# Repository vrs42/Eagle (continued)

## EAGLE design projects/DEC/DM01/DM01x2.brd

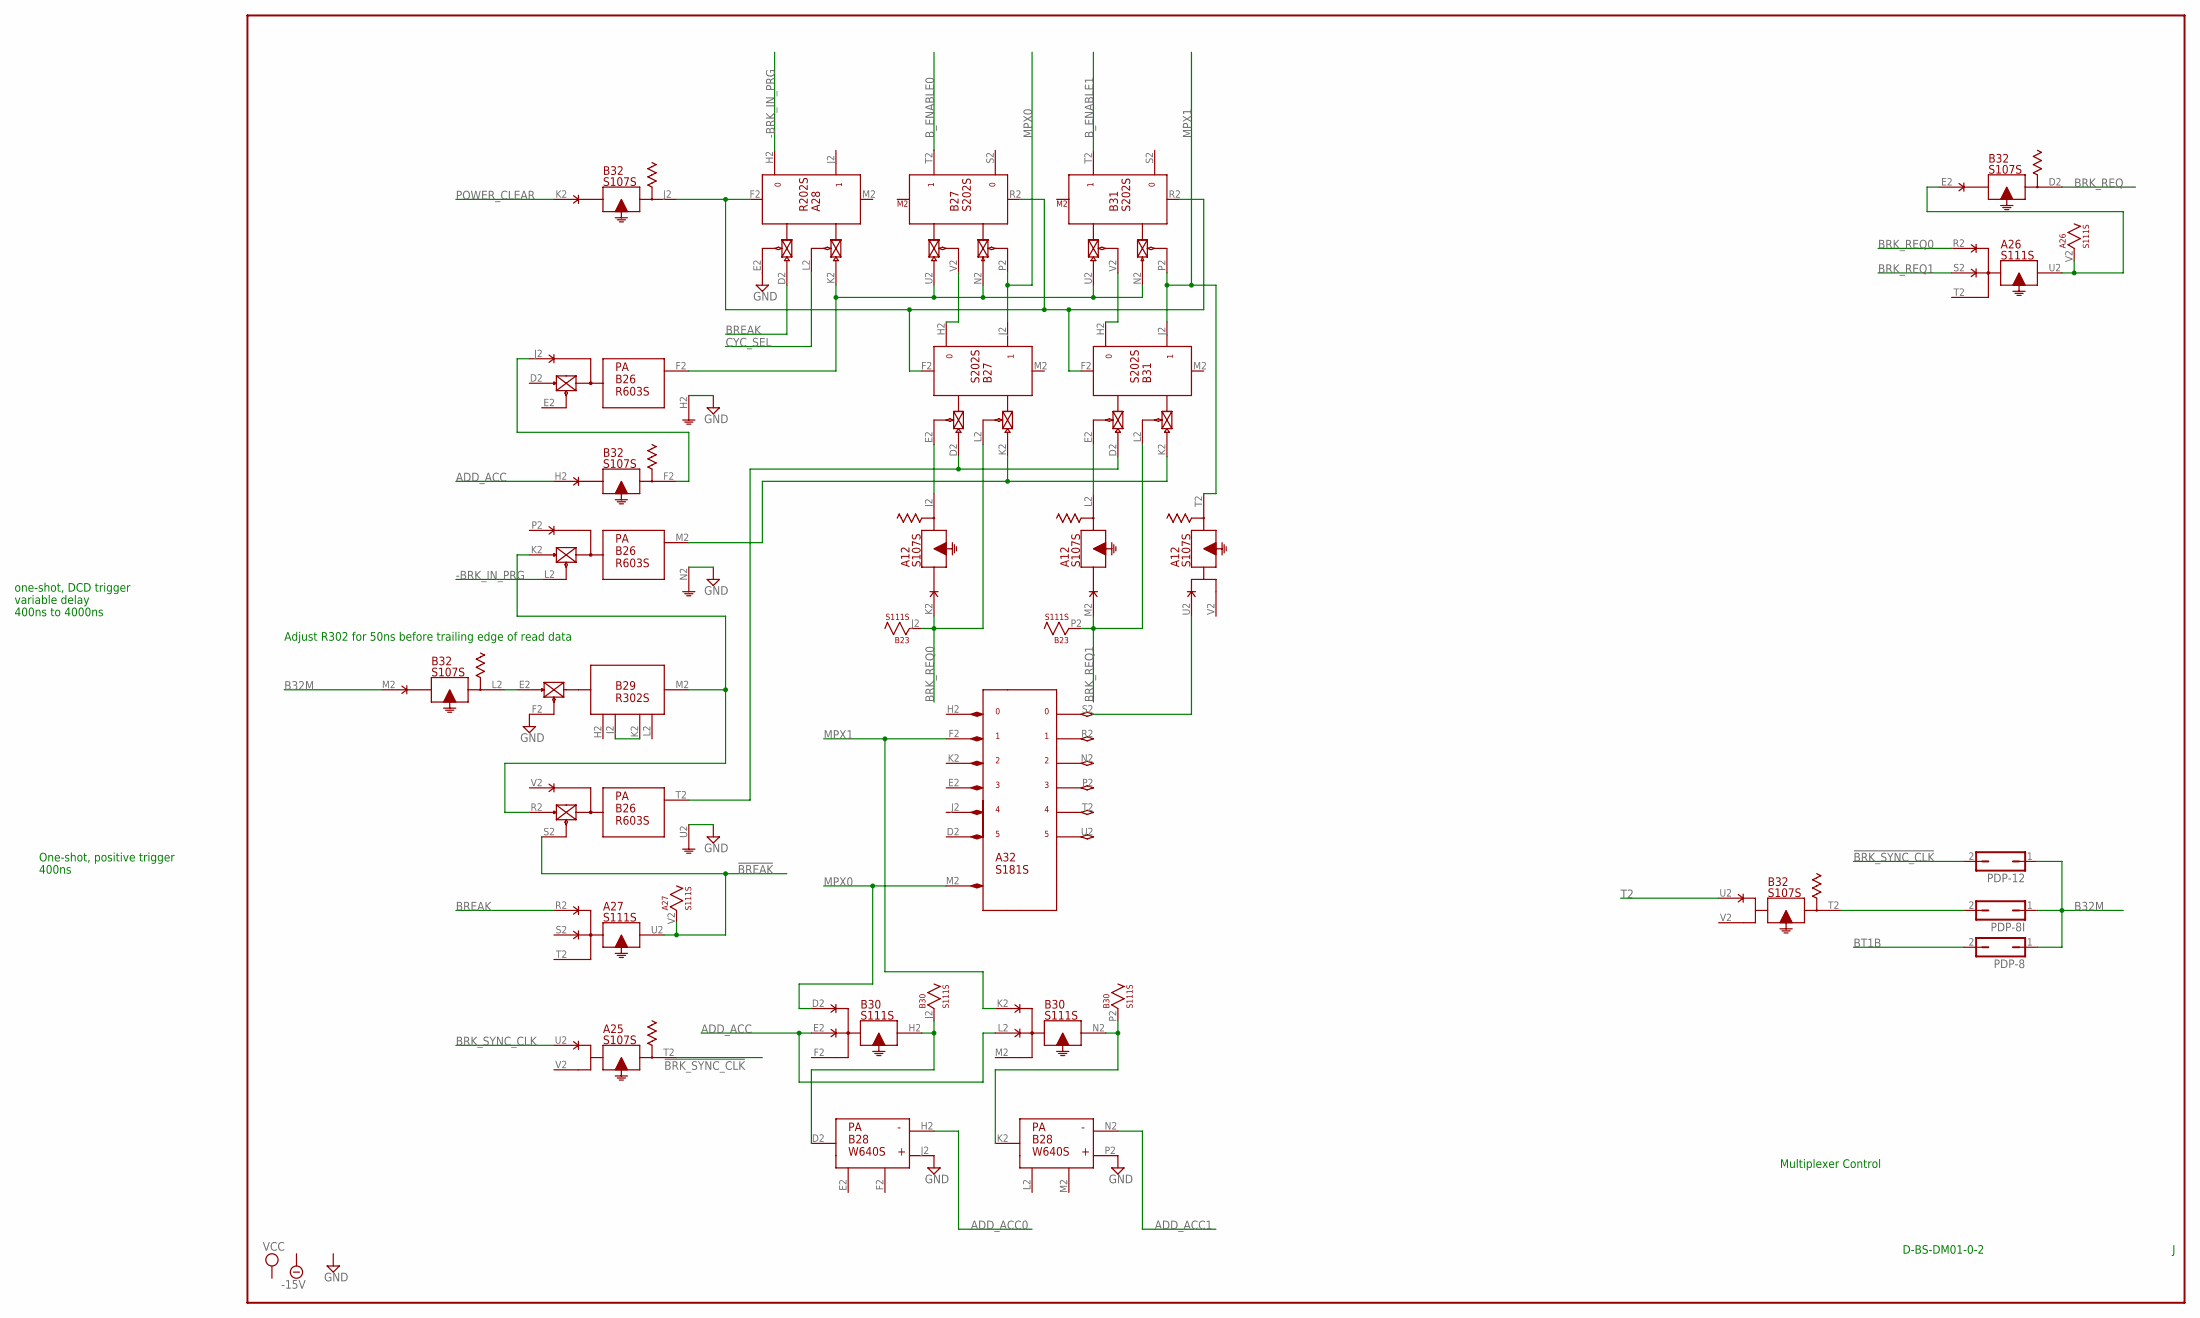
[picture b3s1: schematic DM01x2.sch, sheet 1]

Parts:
A12, A25: S107S; H807S
A26, A27: S111S; H807S
A28: R202S; H807S
A32: S181S; H807S
B23, B30: S111S; H807S
B26: R603S; H807S
B27, B31: S202S; H807S
B28: W640S; H807S
B29: R302S; H807S
B32: S107S; H807S
PDP-8, PDP-8I, PDP-12: JP1Q; JP1

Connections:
!BREAK: A27.U2, A27.V2, B26.S2 (EN0)
!BRK_SYNC_CLK: A25.T2, PDP-12.2
-15V: A12.B2 (-15V), A25.B2 (-15V), A26.B2 (-15V), A27.B2 (-15V), A28.B2 (-15V), A32.B2 (-15V), B23.B2 (-15V), B26.B2 (-15V), B27.B2 (-15V), B28.B2 (-15V), B29.B2 (-15V), B30.B2 (-15V), B31.B2 (-15V), B32.B2 (-15V); also elsewhere on the board
-BRK_IN_PRG: A28.H2 (0), B26.L2 (EN0)
ADD_ACC: B30.E2, B30.L2, B32.H2; also elsewhere on the board
ADD_ACC0: B28.H2 (H); also elsewhere on the board
ADD_ACC1: B28.N2 (H); also elsewhere on the board
B32M: B32.M2, PDP-8.1, PDP-8I.1, PDP-12.1
BREAK: A27.R2, A28.D2 (PU0); also elsewhere on the board
BRK_REQ: B32.D2; also elsewhere on the board
BRK_REQ0: A12.K2, A26.R2, B23.J2, B27.L2 (EN1); also elsewhere on the board
BRK_REQ1: A12.M2, A26.S2, B23.P2, B31.L2 (EN1); also elsewhere on the board
BRK_SYNC_CLK: A25.U2; also elsewhere on the board
BT1B: PDP-8.2; also elsewhere on the board
B_ENABLE0: B27.T2 (1); also elsewhere on the board
B_ENABLE1: B31.T2 (1); also elsewhere on the board
CYC_SEL: A28.L2 (EN1); also elsewhere on the board
GND: A12.C2 (GND), A25.C2 (GND), A26.C2 (GND), A27.C2 (GND), A28.C2 (GND), A28.E2 (EN0), A32.C2 (GND), B23.C2 (GND), B26.C2 (GND), B26.H2 (G), B26.N2 (G), B26.U2 (G), B27.C2 (GND), B28.C2 (GND), B28.J2 (J), B28.P2 (J), B29.C2 (GND), B29.F2 (F), B30.C2 (GND), B31.C2 (GND), B32.C2 (GND); also elsewhere on the board
MPX0: A32.M2 (M), B27.J2 (1), B27.P2 (EN0), B30.D2; also elsewhere on the board
MPX1: A12.T2, A32.F2 (F), B30.K2, B31.J2 (1), B31.P2 (EN0); also elsewhere on the board
unnamed: A28.F2 (RESET), B27.F2 (RESET), B27.R2 (RESET), B31.F2 (RESET), B31.R2 (RESET), B32.J2
unnamed: B26.J2, B32.F2
unnamed: B32.T2, PDP-8I.2
unnamed: B26.K2 (PU0), B26.R2 (PU0), B29.M2 (M)
unnamed: B27.H2 (0), B27.V2 (EN1)
unnamed: B31.H2 (0), B31.V2 (EN1)
unnamed: B26.M2 (O), B27.K2 (PU1), B31.K2 (PU1)
unnamed: A28.K2 (PU1), B26.F2 (O), B27.N2 (PU0), B27.U2 (PU1), B31.N2 (PU0), B31.U2 (PU1)
unnamed: A26.U2, A26.V2, B32.E2
unnamed: A12.J2, B27.E2 (EN0)
unnamed: A12.L2, B31.E2 (EN0)
unnamed: B28.D2 (D), B30.H2, B30.J2
unnamed: B26.T2 (O), B27.D2 (PU0), B31.D2 (PU0)
unnamed: B28.K2 (D), B30.N2, B30.P2
unnamed: A12.U2, A32.S2 (S)
unnamed: B29.E2 (E), B32.L2
unnamed: B29.J2 (J), B29.K2 (K)
POWER_CLEAR: B32.K2; also elsewhere on the board
T2: B32.U2; also elsewhere on the board
VCC: A12.A2 (VCC), A25.A2 (VCC), A26.A2 (VCC), A27.A2 (VCC), A28.A2 (VCC), A32.A2 (VCC), B23.A2 (VCC), B26.A2 (VCC), B27.A2 (VCC), B28.A2 (VCC), B29.A2 (VCC), B30.A2 (VCC), B31.A2 (VCC), B32.A2 (VCC); also elsewhere on the board

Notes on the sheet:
Multiplexer Control
D-BS-DM01-0-2
one-shot, DCD trigger
variable delay
400ns to 4000ns
400ns
One-shot, positive trigger
Adjust R302 for 50ns before trailing edge of read data

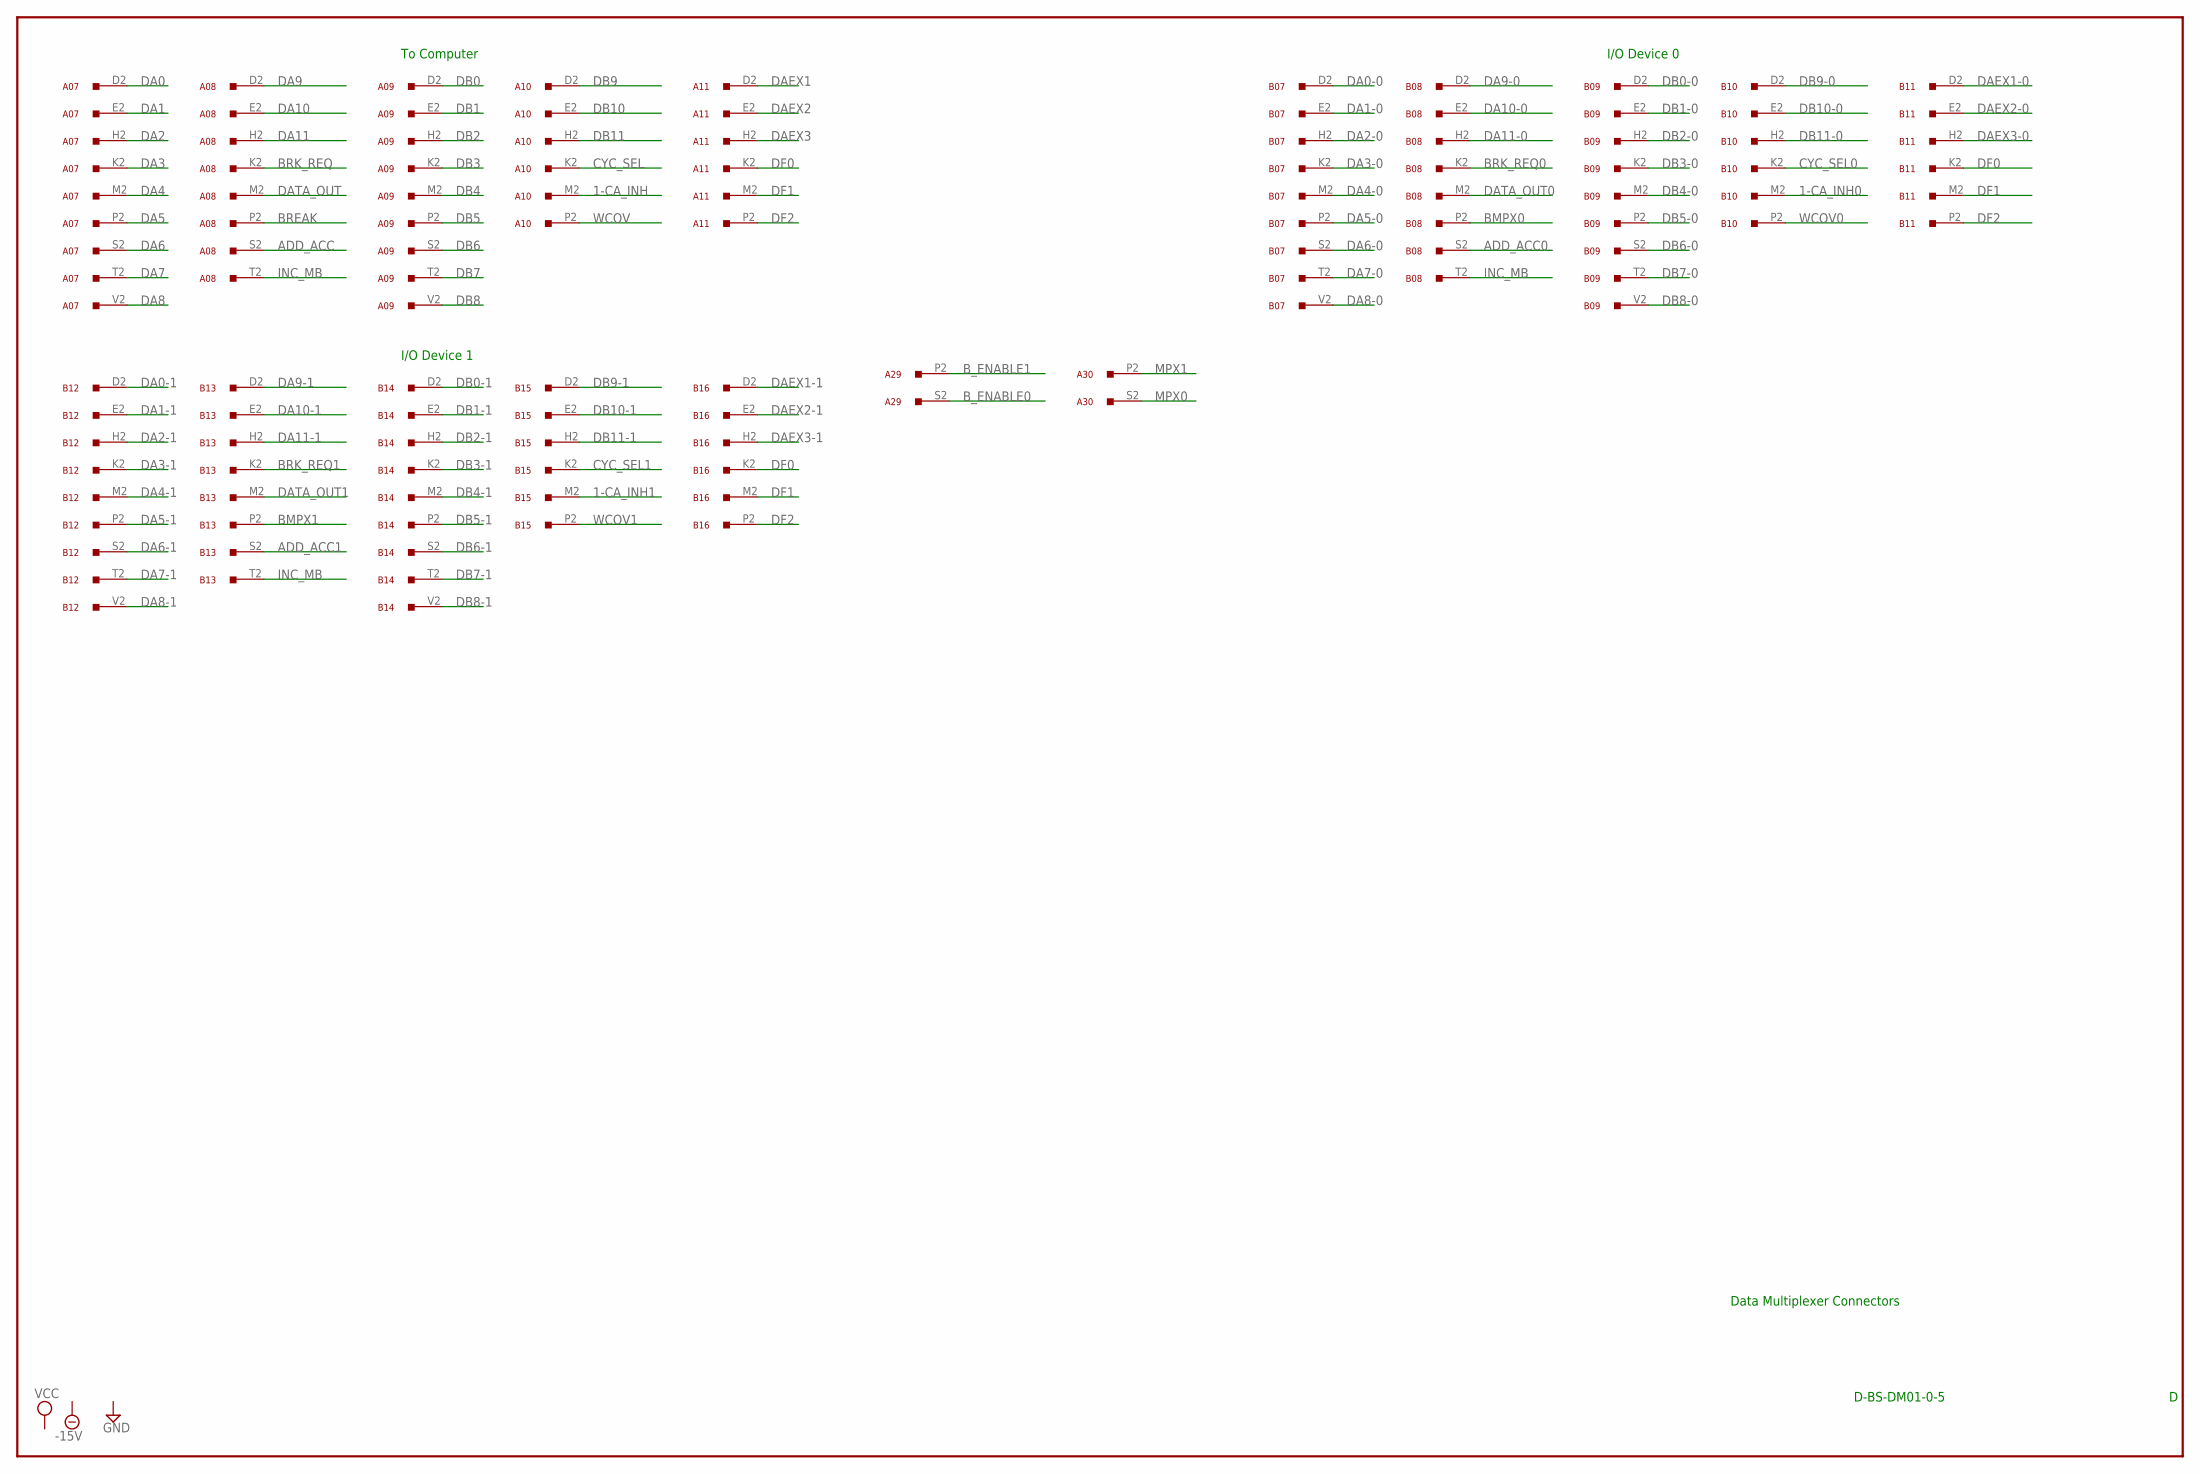
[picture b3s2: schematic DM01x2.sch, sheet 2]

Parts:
A07, A08, A09, A10, A11, A29, A30: W021S; H807S
B07, B08, B09, B10, B11, B12, B13, B14, B15, B16: W021S; H807S

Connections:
1-CA_INH: A10.M2; also elsewhere on the board
1-CA_INH0: B10.M2; also elsewhere on the board
1-CA_INH1: B15.M2; also elsewhere on the board
ADD_ACC: A08.S2; also elsewhere on the board
ADD_ACC0: B08.S2; also elsewhere on the board
ADD_ACC1: B13.S2; also elsewhere on the board
BMPX0: B08.P2; also elsewhere on the board
BMPX1: B13.P2; also elsewhere on the board
BREAK: A08.P2; also elsewhere on the board
BRK_REQ: A08.K2; also elsewhere on the board
BRK_REQ0: B08.K2; also elsewhere on the board
BRK_REQ1: B13.K2; also elsewhere on the board
B_ENABLE0: A29.S2; also elsewhere on the board
B_ENABLE1: A29.P2; also elsewhere on the board
CYC_SEL: A10.K2; also elsewhere on the board
CYC_SEL0: B10.K2; also elsewhere on the board
CYC_SEL1: B15.K2; also elsewhere on the board
DA0: A07.D2; also elsewhere on the board
DA0-0: B07.D2; also elsewhere on the board
DA0-1: B12.D2; also elsewhere on the board
DA1: A07.E2; also elsewhere on the board
DA1-0: B07.E2; also elsewhere on the board
DA1-1: B12.E2; also elsewhere on the board
DA2: A07.H2; also elsewhere on the board
DA2-0: B07.H2; also elsewhere on the board
DA2-1: B12.H2; also elsewhere on the board
DA3: A07.K2; also elsewhere on the board
DA3-0: B07.K2; also elsewhere on the board
DA3-1: B12.K2; also elsewhere on the board
DA4: A07.M2; also elsewhere on the board
DA4-0: B07.M2; also elsewhere on the board
DA4-1: B12.M2; also elsewhere on the board
DA5: A07.P2; also elsewhere on the board
DA5-0: B07.P2; also elsewhere on the board
DA5-1: B12.P2; also elsewhere on the board
DA6: A07.S2; also elsewhere on the board
DA6-0: B07.S2; also elsewhere on the board
DA6-1: B12.S2; also elsewhere on the board
DA7: A07.T2; also elsewhere on the board
DA7-0: B07.T2; also elsewhere on the board
DA7-1: B12.T2; also elsewhere on the board
DA8: A07.V2; also elsewhere on the board
DA8-0: B07.V2; also elsewhere on the board
DA8-1: B12.V2; also elsewhere on the board
DA9: A08.D2; also elsewhere on the board
DA9-0: B08.D2; also elsewhere on the board
DA9-1: B13.D2; also elsewhere on the board
DA10: A08.E2; also elsewhere on the board
DA10-0: B08.E2; also elsewhere on the board
DA10-1: B13.E2; also elsewhere on the board
DA11: A08.H2; also elsewhere on the board
DA11-0: B08.H2; also elsewhere on the board
DA11-1: B13.H2; also elsewhere on the board
DAEX1: A11.D2; also elsewhere on the board
DAEX1-0: B11.D2; also elsewhere on the board
DAEX1-1: B16.D2; also elsewhere on the board
DAEX2: A11.E2; also elsewhere on the board
DAEX2-0: B11.E2; also elsewhere on the board
DAEX2-1: B16.E2; also elsewhere on the board
DAEX3: A11.H2; also elsewhere on the board
DAEX3-0: B11.H2; also elsewhere on the board
DAEX3-1: B16.H2; also elsewhere on the board
DATA_OUT: A08.M2; also elsewhere on the board
DATA_OUT0: B08.M2; also elsewhere on the board
DATA_OUT1: B13.M2; also elsewhere on the board
DB0: A09.D2; also elsewhere on the board
DB0-0: B09.D2; also elsewhere on the board
DB0-1: B14.D2; also elsewhere on the board
DB1: A09.E2; also elsewhere on the board
DB1-0: B09.E2; also elsewhere on the board
DB1-1: B14.E2; also elsewhere on the board
DB2: A09.H2; also elsewhere on the board
DB2-0: B09.H2; also elsewhere on the board
DB2-1: B14.H2; also elsewhere on the board
DB3: A09.K2; also elsewhere on the board
DB3-0: B09.K2; also elsewhere on the board
DB3-1: B14.K2; also elsewhere on the board
DB4: A09.M2; also elsewhere on the board
DB4-0: B09.M2; also elsewhere on the board
DB4-1: B14.M2; also elsewhere on the board
DB5: A09.P2; also elsewhere on the board
DB5-0: B09.P2; also elsewhere on the board
DB5-1: B14.P2; also elsewhere on the board
DB6: A09.S2; also elsewhere on the board
DB6-0: B09.S2; also elsewhere on the board
DB6-1: B14.S2; also elsewhere on the board
DB7: A09.T2; also elsewhere on the board
DB7-0: B09.T2; also elsewhere on the board
DB7-1: B14.T2; also elsewhere on the board
DB8: A09.V2; also elsewhere on the board
DB8-0: B09.V2; also elsewhere on the board
DB8-1: B14.V2; also elsewhere on the board
DB9: A10.D2; also elsewhere on the board
DB9-0: B10.D2; also elsewhere on the board
DB9-1: B15.D2; also elsewhere on the board
DB10: A10.E2; also elsewhere on the board
DB10-0: B10.E2; also elsewhere on the board
DB10-1: B15.E2; also elsewhere on the board
DB11: A10.H2; also elsewhere on the board
DB11-0: B10.H2; also elsewhere on the board
DB11-1: B15.H2; also elsewhere on the board
DF0: A11.K2, B11.K2, B16.K2
DF1: A11.M2, B11.M2, B16.M2
DF2: A11.P2, B11.P2, B16.P2
GND: A07.C2 (GND), A07.F2 (GND), A07.J2 (GND), A07.L2 (GND), A07.N2 (GND), A07.R2 (GND), A07.U2 (GND), A08.C2 (GND), A08.F2 (GND), A08.J2 (GND), A08.L2 (GND), A08.N2 (GND), A08.R2 (GND), A08.U2 (GND), A09.C2 (GND), A09.F2 (GND), A09.J2 (GND), A09.L2 (GND), A09.N2 (GND), A09.R2 (GND), A09.U2 (GND), A10.C2 (GND), A10.F2 (GND), A10.J2 (GND), A10.L2 (GND), A10.N2 (GND), A10.R2 (GND), A10.U2 (GND), A11.C2 (GND), A11.F2 (GND), A11.J2 (GND), A11.L2 (GND), A11.N2 (GND), A11.R2 (GND), A11.U2 (GND), A29.C2 (GND), A29.F2 (GND), A29.J2 (GND), A29.L2 (GND), A29.N2 (GND), A29.R2 (GND), A29.U2 (GND), A30.C2 (GND), A30.F2 (GND), A30.J2 (GND), A30.L2 (GND), A30.N2 (GND), A30.R2 (GND), A30.U2 (GND), B07.C2 (GND), B07.F2 (GND), B07.J2 (GND), B07.L2 (GND), B07.N2 (GND), B07.R2 (GND), B07.U2 (GND), B08.C2 (GND), B08.F2 (GND), B08.J2 (GND), B08.L2 (GND), B08.N2 (GND), B08.R2 (GND), B08.U2 (GND), B09.C2 (GND), B09.F2 (GND), B09.J2 (GND), B09.L2 (GND), B09.N2 (GND), B09.R2 (GND), B09.U2 (GND), B10.C2 (GND), B10.F2 (GND), B10.J2 (GND), B10.L2 (GND), B10.N2 (GND), B10.R2 (GND), B10.U2 (GND), B11.C2 (GND), B11.F2 (GND), B11.J2 (GND), B11.L2 (GND), B11.N2 (GND), B11.R2 (GND), B11.U2 (GND), B12.C2 (GND), B12.F2 (GND), B12.J2 (GND), B12.L2 (GND), B12.N2 (GND), B12.R2 (GND), B12.U2 (GND), B13.C2 (GND), B13.F2 (GND), B13.J2 (GND), B13.L2 (GND), B13.N2 (GND), B13.R2 (GND), B13.U2 (GND), B14.C2 (GND), B14.F2 (GND), B14.J2 (GND), B14.L2 (GND), B14.N2 (GND), B14.R2 (GND), B14.U2 (GND), B15.C2 (GND), B15.F2 (GND), B15.J2 (GND), B15.L2 (GND), B15.N2 (GND), B15.R2 (GND), B15.U2 (GND), B16.C2 (GND), B16.F2 (GND), B16.J2 (GND), B16.L2 (GND), B16.N2 (GND), B16.R2 (GND), B16.U2 (GND); also elsewhere on the board
INC_MB: A08.T2, B08.T2, B13.T2
MPX0: A30.S2; also elsewhere on the board
MPX1: A30.P2; also elsewhere on the board
WCOV: A10.P2; also elsewhere on the board
WCOV0: B10.P2; also elsewhere on the board
WCOV1: B15.P2; also elsewhere on the board

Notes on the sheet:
D-BS-DM01-0-5
Data Multiplexer Connectors
To Computer
I/O Device 0
I/O Device 1

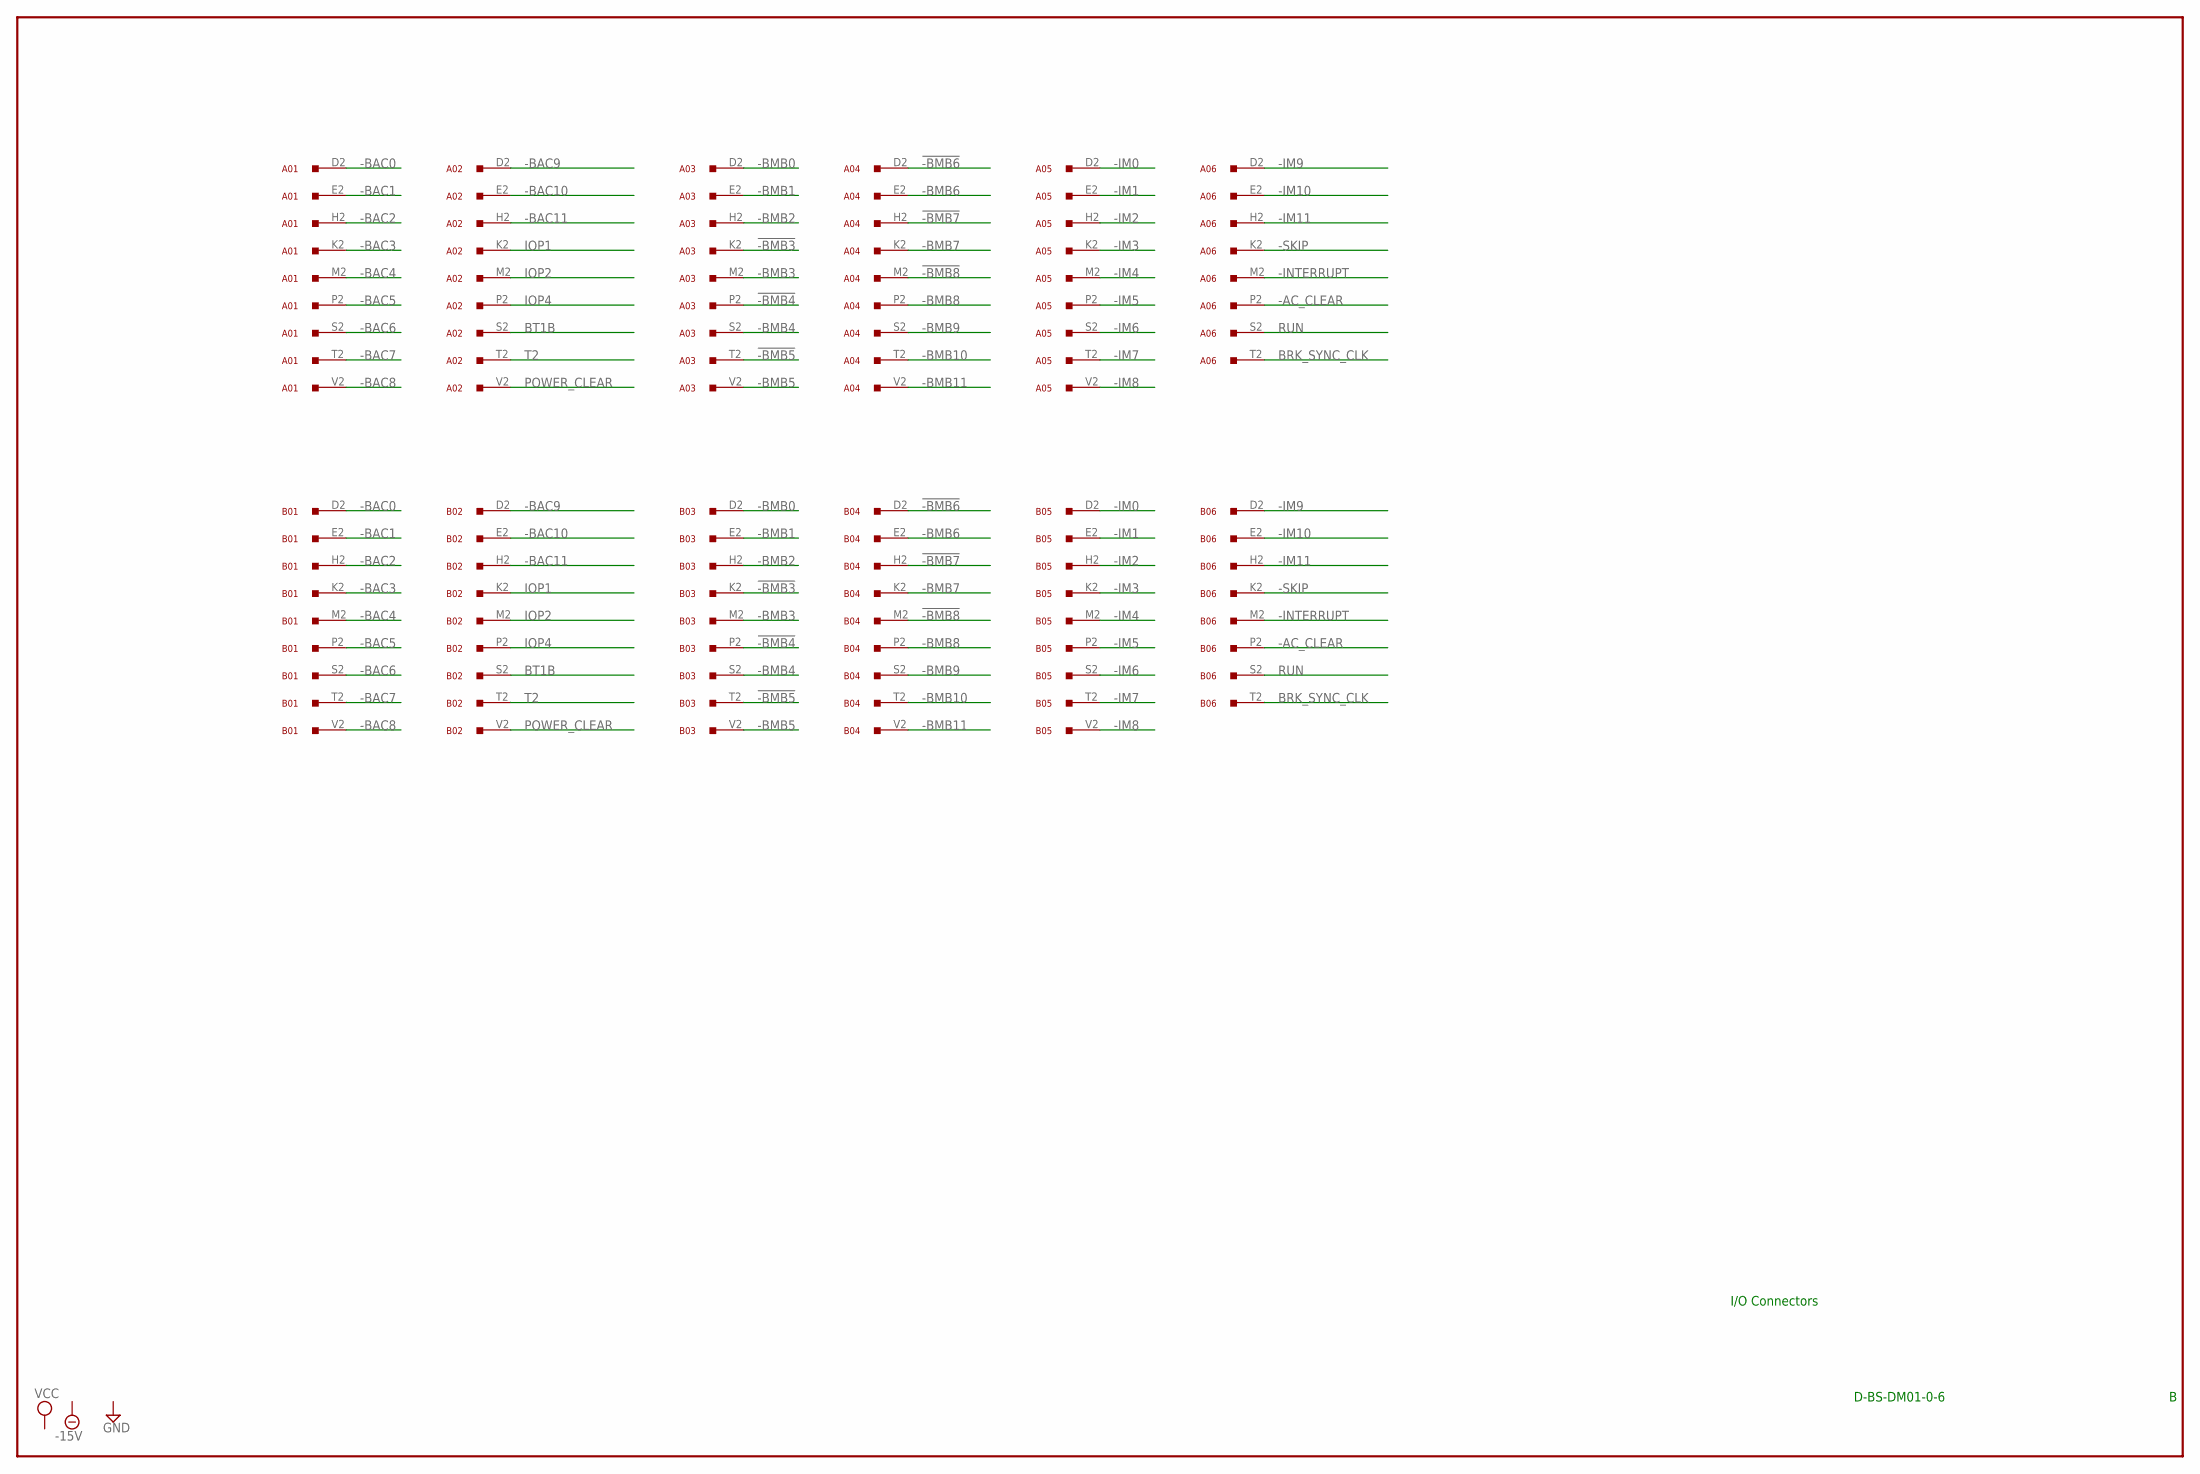
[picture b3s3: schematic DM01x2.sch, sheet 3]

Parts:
A01, A02, A03, A04, A05, A06: W021S; H807S
B01, B02, B03, B04, B05, B06: W021S; H807S

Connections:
!-BMB3: A03.K2, B03.K2
!-BMB4: A03.P2, B03.P2
!-BMB5: A03.T2, B03.T2
!-BMB6: A04.D2, B04.D2
!-BMB7: A04.H2, B04.H2
!-BMB8: A04.M2, B04.M2
-AC_CLEAR: A06.P2, B06.P2
-BAC0: A01.D2, B01.D2
-BAC1: A01.E2, B01.E2
-BAC2: A01.H2, B01.H2
-BAC3: A01.K2, B01.K2
-BAC4: A01.M2, B01.M2
-BAC5: A01.P2, B01.P2
-BAC6: A01.S2, B01.S2
-BAC7: A01.T2, B01.T2
-BAC8: A01.V2, B01.V2
-BAC9: A02.D2, B02.D2
-BAC10: A02.E2, B02.E2
-BAC11: A02.H2, B02.H2
-BMB0: A03.D2, B03.D2
-BMB1: A03.E2, B03.E2
-BMB2: A03.H2, B03.H2
-BMB3: A03.M2, B03.M2
-BMB4: A03.S2, B03.S2
-BMB5: A03.V2, B03.V2
-BMB6: A04.E2, B04.E2
-BMB7: A04.K2, B04.K2
-BMB8: A04.P2, B04.P2
-BMB9: A04.S2, B04.S2
-BMB10: A04.T2, B04.T2
-BMB11: A04.V2, B04.V2
-IM0: A05.D2, B05.D2
-IM1: A05.E2, B05.E2
-IM2: A05.H2, B05.H2
-IM3: A05.K2, B05.K2
-IM4: A05.M2, B05.M2
-IM5: A05.P2, B05.P2
-IM6: A05.S2, B05.S2
-IM7: A05.T2, B05.T2
-IM8: A05.V2, B05.V2
-IM9: A06.D2, B06.D2
-IM10: A06.E2, B06.E2
-IM11: A06.H2, B06.H2
-INTERRUPT: A06.M2, B06.M2
-SKIP: A06.K2, B06.K2
BRK_SYNC_CLK: A06.T2, B06.T2; also elsewhere on the board
BT1B: A02.S2, B02.S2; also elsewhere on the board
GND: A01.C2 (GND), A01.F2 (GND), A01.J2 (GND), A01.L2 (GND), A01.N2 (GND), A01.R2 (GND), A01.U2 (GND), A02.C2 (GND), A02.F2 (GND), A02.J2 (GND), A02.L2 (GND), A02.N2 (GND), A02.R2 (GND), A02.U2 (GND), A03.C2 (GND), A03.F2 (GND), A03.J2 (GND), A03.L2 (GND), A03.N2 (GND), A03.R2 (GND), A03.U2 (GND), A04.C2 (GND), A04.F2 (GND), A04.J2 (GND), A04.L2 (GND), A04.N2 (GND), A04.R2 (GND), A04.U2 (GND), A05.C2 (GND), A05.F2 (GND), A05.J2 (GND), A05.L2 (GND), A05.N2 (GND), A05.R2 (GND), A05.U2 (GND), A06.C2 (GND), A06.F2 (GND), A06.J2 (GND), A06.L2 (GND), A06.N2 (GND), A06.R2 (GND), A06.U2 (GND), B01.C2 (GND), B01.F2 (GND), B01.J2 (GND), B01.L2 (GND), B01.N2 (GND), B01.R2 (GND), B01.U2 (GND), B02.C2 (GND), B02.F2 (GND), B02.J2 (GND), B02.L2 (GND), B02.N2 (GND), B02.R2 (GND), B02.U2 (GND), B03.C2 (GND), B03.F2 (GND), B03.J2 (GND), B03.L2 (GND), B03.N2 (GND), B03.R2 (GND), B03.U2 (GND), B04.C2 (GND), B04.F2 (GND), B04.J2 (GND), B04.L2 (GND), B04.N2 (GND), B04.R2 (GND), B04.U2 (GND), B05.C2 (GND), B05.F2 (GND), B05.J2 (GND), B05.L2 (GND), B05.N2 (GND), B05.R2 (GND), B05.U2 (GND), B06.C2 (GND), B06.F2 (GND), B06.J2 (GND), B06.L2 (GND), B06.N2 (GND), B06.R2 (GND), B06.U2 (GND); also elsewhere on the board
IOP1: A02.K2, B02.K2
IOP2: A02.M2, B02.M2
IOP4: A02.P2, B02.P2
POWER_CLEAR: A02.V2, B02.V2; also elsewhere on the board
RUN: A06.S2, B06.S2
T2: A02.T2, B02.T2; also elsewhere on the board

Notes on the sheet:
D-BS-DM01-0-6
I/O Connectors

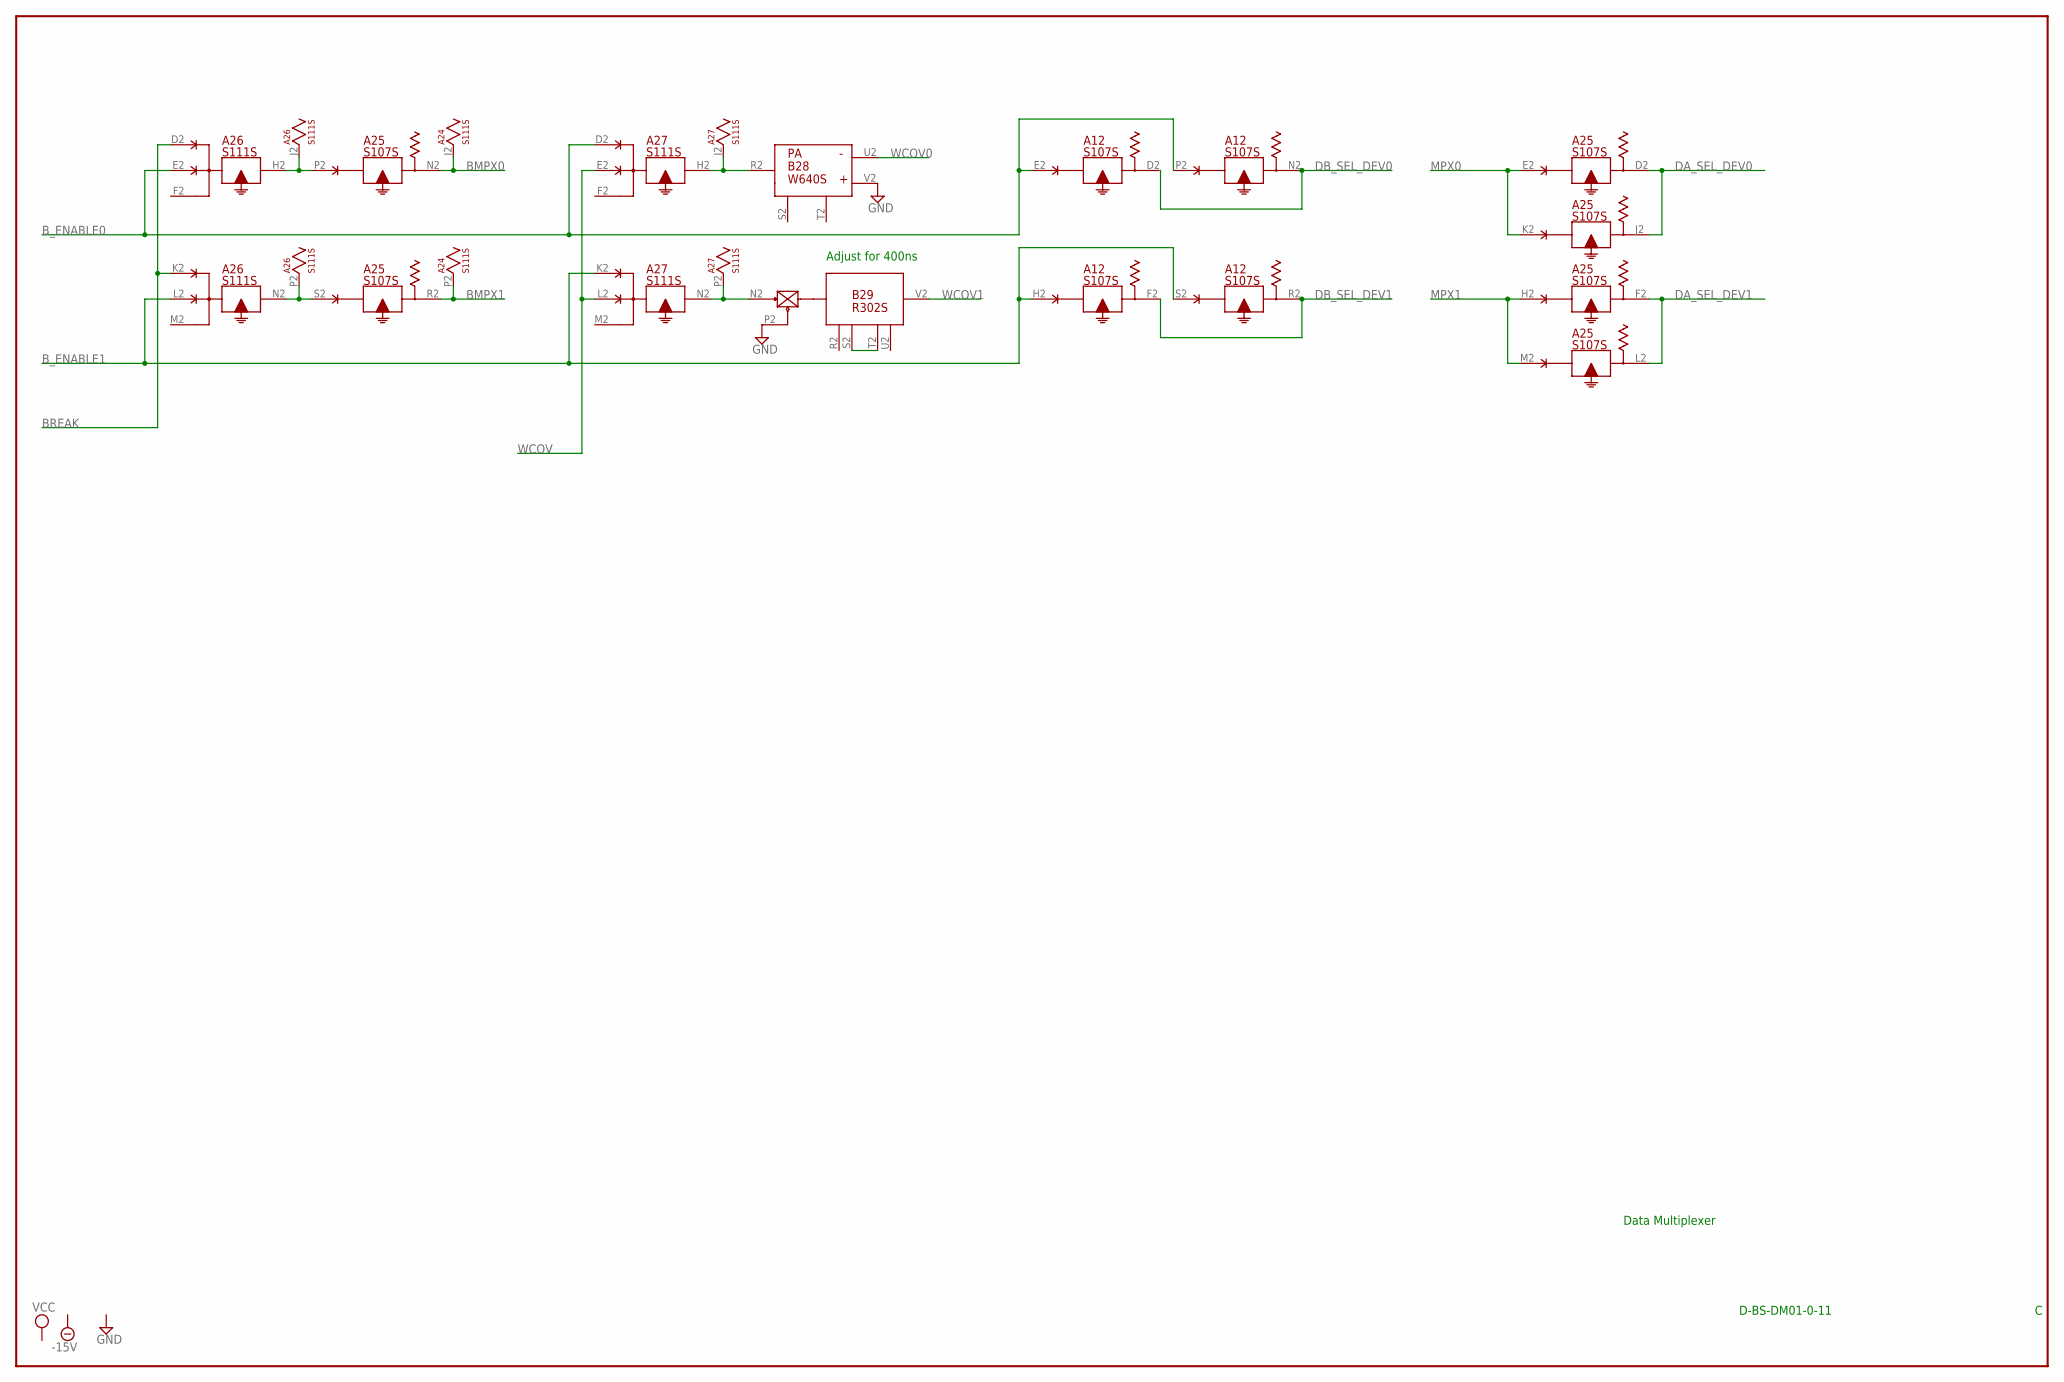
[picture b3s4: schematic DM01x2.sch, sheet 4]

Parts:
A12, A25: S107S; H807S
A24, A26, A27: S111S; H807S
B28: W640S; H807S
B29: R302S; H807S

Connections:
-15V: A12.B2 (-15V), A24.B2 (-15V), A25.B2 (-15V), A26.B2 (-15V), A27.B2 (-15V), B28.B2 (-15V), B29.B2 (-15V); also elsewhere on the board
BMPX0: A24.J2, A25.N2; also elsewhere on the board
BMPX1: A24.P2, A25.R2; also elsewhere on the board
BREAK: A26.D2, A26.K2; also elsewhere on the board
B_ENABLE0: A12.E2, A12.P2, A26.E2, A27.D2; also elsewhere on the board
B_ENABLE1: A12.H2, A12.S2, A26.L2, A27.K2; also elsewhere on the board
DA_SEL_DEV0: A25.D2, A25.J2; also elsewhere on the board
DA_SEL_DEV1: A25.F2, A25.L2; also elsewhere on the board
DB_SEL_DEV0: A12.D2, A12.N2; also elsewhere on the board
DB_SEL_DEV1: A12.F2, A12.R2; also elsewhere on the board
GND: A12.C2 (GND), A24.C2 (GND), A25.C2 (GND), A26.C2 (GND), A27.C2 (GND), B28.C2 (GND), B28.V2 (J), B29.C2 (GND), B29.P2 (F); also elsewhere on the board
MPX0: A25.E2, A25.K2; also elsewhere on the board
MPX1: A25.H2, A25.M2; also elsewhere on the board
unnamed: A27.H2, A27.J2, B28.R2 (D)
unnamed: A27.N2, A27.P2, B29.N2 (E)
unnamed: B29.S2 (J), B29.T2 (K)
unnamed: A25.P2, A26.H2, A26.J2
unnamed: A25.S2, A26.N2, A26.P2
VCC: A12.A2 (VCC), A24.A2 (VCC), A25.A2 (VCC), A26.A2 (VCC), A27.A2 (VCC), B28.A2 (VCC), B29.A2 (VCC); also elsewhere on the board
WCOV: A27.E2, A27.L2; also elsewhere on the board
WCOV0: B28.U2 (H); also elsewhere on the board
WCOV1: B29.V2 (M); also elsewhere on the board

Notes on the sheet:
D-BS-DM01-0-11
Data Multiplexer
Adjust for 400ns
